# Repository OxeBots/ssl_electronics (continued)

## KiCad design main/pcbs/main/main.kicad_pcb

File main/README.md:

# SSL Electronics - Oxebots

Electronics design for the RoboCup Soccer Small-Size League (SSL).

## System Architecture

*   **Main Board:** ESP32-based controller board.
*   **Power Board:** Power distribution and battery protection.
*   **Kicker Board:** Board that drives the solenoid through a capacitor bank charged up to 200V.

## Repository Structure

*   `/pcbs`: KiCad boards project files.
*   `/Libraries`: Custom symbols, footprints, and 3D models.
*   `/exported`: STEP and 3D exports.
*   `/datasheets`: Component documentation.

## Core Components

*   **Toolchain:** KiCad 9.0+
*   **MCU:** ESP32 38-pin
*   **RF:** NRF24L01+
*   **Sensors:** GY-85 (IMU), AS5600 (motor encoder), VL53L5X (ToF sensor)
*   **Motors:** BL48250 motor with driver board (for 24V).
*   **Solenoid:** 25X50TL (for 24V)

## Configuration

To resolve library dependencies in KiCad, you must configure the `OXEBOTS_SSL_LIB_DIR` path variable:

1.  Open KiCad.
2.  Go to **Preferences** > **Configure Paths...**
3.  Add a new entry (+ symbol):
    *   **Name:** `OXEBOTS_SSL_LIB_DIR`
    *   **Path:** Path to the `Libraries` folder in your local machine.

This ensures all schematic symbols, footprints, and 3D models are correctly linked.

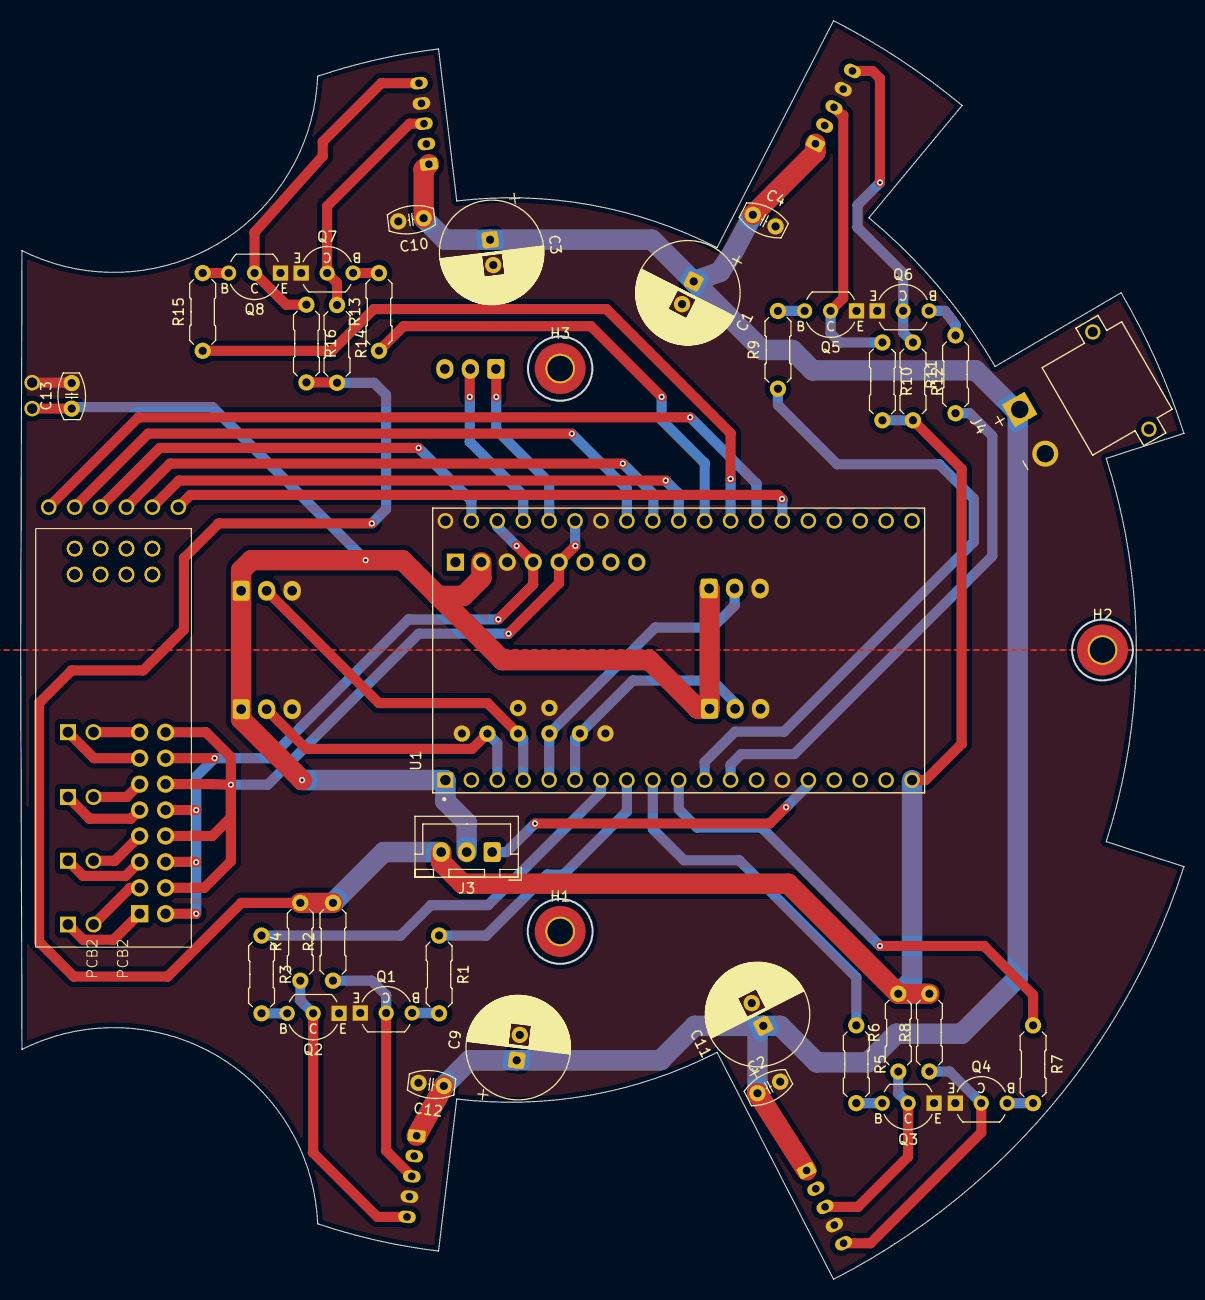
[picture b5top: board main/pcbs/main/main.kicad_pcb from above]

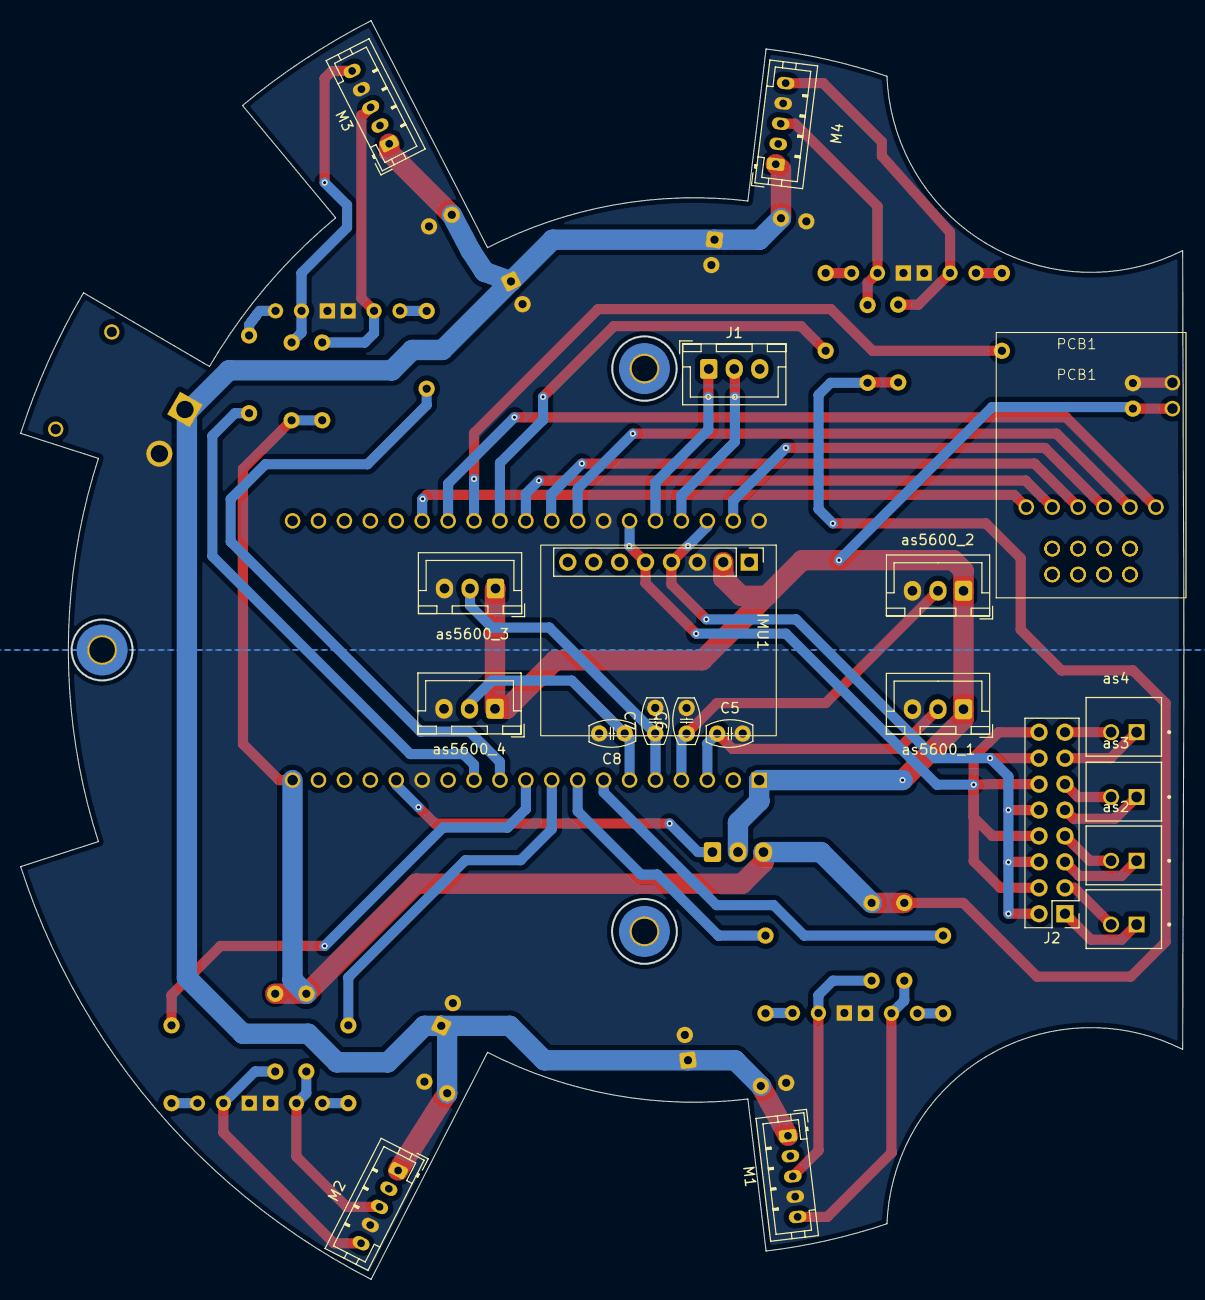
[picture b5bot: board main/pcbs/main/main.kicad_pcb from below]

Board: 2 copper layers, 114.0 x 123.3 mm, 60 parts (20 on the bottom side), 59 nets.

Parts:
C1, C3, C9, C11: 47uF; CP_Radial_D10.0mm_P2.50mm
C2, C4, C5, C6, C7, C8, C10, C12, C13: 100 nF; C_Disc_D5.0mm_W2.5mm_P2.50mm
H1, H2, H3: MountingHole; MountingHole_2.5mm_Pad_TopBottom
IMU1: GY 85; GY-085
J1, J3: JST_XH_B3B; JST_XH_B3B-XH-A_1x03_P2.50mm_Vertical
J2: Jumpers; PinHeader_2x08_P2.54mm_Vertical
J4: XT30PW-M; AMASS_XT30PW-M
M1, M2, M3, M4: HY-5_P2.00mm_Vertical
PCB1: NRF24L01_PWR_ADP
PCB2: NRF24L01
Q1, Q2, Q3, Q4, Q5, Q6, Q7, Q8: 2SC945; TO-92_Inline_Wide_ECB
R1, R2, R3, R4, R5, R6, R7, R8, R9, R10, R11, R12, R13, R14, R15, R16: 10k; R_Axial_DIN0207_L6.3mm_D2.5mm_P7.62mm_Horizontal
U1: ESP32-DEVKITC-32U; MODULE_ESP32-DEVKITC-32U
as1: M1_ENC_I2C; JST_B2B-XH-A
as2: M2_ENC_I2C; JST_B2B-XH-A
as3: M3_ENC_I2C; JST_B2B-XH-A
as4: M4_ENC_I2C; JST_B2B-XH-A
as5600_1: M1_ENC_AN; JST_XH_B3B-XH-A_1x03_P2.50mm_Vertical
as5600_2: M2_ENC_AN; JST_XH_B3B-XH-A_1x03_P2.50mm_Vertical
as5600_3: M3_ENC_AN; JST_XH_B3B-XH-A_1x03_P2.50mm_Vertical
as5600_4: M4_ENC_AN; JST_XH_B3B-XH-A_1x03_P2.50mm_Vertical

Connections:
+3.3V: C13.1, IMU1.2, J3.2, PCB1.15 (VCC), U1.1 (3V3), as5600_1.1, as5600_2.1, as5600_3.1, as5600_4.1
+5V: J3.3, R2.2, R4.2, R6.2, R8.2, R10.2, R12.2, R14.2, R16.2, U1.19 (EXT_5V)
+24V: C1.1, C2.1, C3.1, C4.1, C9.1, C10.1, C11.1, C12.1, J4.P, M1.1 (VCC), M2.1 (VCC), M3.1 (VCC), M4.1 (VCC)
/esp32/I2C.SCL: IMU1.4, J2.2, J2.6, J2.10, J2.14, U1.36 (IO22)
/esp32/I2C.SDA: IMU1.5, J2.4, J2.8, J2.12, J2.16, U1.33 (IO21)
/esp32/KICKER_EN: J1.1, U1.34 (RXD0)
/esp32/KICKER_PWM: J1.2, U1.35 (TXD0)
/esp32/M1_DIR: R1.1, U1.8 (IO33)
/esp32/M1_ENC: C5.1, U1.3 (SENSOR_VP), as5600_1.2
/esp32/M1_PWM: R3.1, U1.7 (IO32)
/esp32/M2_DIR: R5.1, U1.9 (IO25)
/esp32/M2_ENC: C6.1, U1.4 (SENSOR_VN), as5600_2.2
/esp32/M2_PWM: R7.1, U1.10 (IO26)
/esp32/M3_DIR: R9.1, U1.11 (IO27)
/esp32/M3_ENC: C7.1, U1.5 (IO34), as5600_3.2
/esp32/M3_PWM: R11.1, U1.12 (IO14)
/esp32/M4_DIR: R13.1, U1.28 (IO17)
/esp32/M4_ENC: C8.1, U1.6 (IO35), as5600_4.2
/esp32/M4_PWM: R15.1, U1.27 (IO16)
/esp32/RADIO.CE: PCB1.9 (CE_{mcu}), U1.25 (IO0)
/esp32/RADIO.CLK: PCB1.11 (SCK_{mcu}), U1.30 (IO18)
/esp32/RADIO.CS: PCB1.10 (CSN_{mcu}), U1.29 (IO5)
/esp32/RADIO.IRQ: PCB1.14 (IRQ_{mcu}), U1.26 (IO4)
/esp32/RADIO.MISO: PCB1.13 (MISO_{mcu}), U1.31 (IO19)
/esp32/RADIO.MOSI: PCB1.12 (MOSI_{mcu}), U1.37 (IO23)
/esp32/V_{MON}: J3.1, U1.15 (IO13)
GND: C1.2, C2.2, C3.2, C4.2, C5.2, C6.2, C7.2, C8.2, C9.2, C10.2, C11.2, C12.2, C13.2, IMU1.3, J4.N, M1.4 (GND), M2.4 (GND), M3.4 (GND), M4.4 (GND), PCB1.16 (GND), Q1.1 (E), Q2.1 (E), Q3.1 (E), Q4.1 (E), Q5.1 (E), Q6.1 (E), Q7.1 (E), Q8.1 (E), U1.14 (GND1), U1.32 (GND2), U1.38 (GND3), as5600_1.3, as5600_2.3, as5600_3.3, as5600_4.3
unnamed: J2.1, as1.1
unnamed: J2.3, as1.2
unnamed: J2.5, as2.1
unnamed: J2.7, as2.2
unnamed: J2.9, as3.1
unnamed: J2.11, as3.2
unnamed: J2.13, as4.1
unnamed: J2.15, as4.2
unnamed: M1.3 (DIR), Q1.2 (C), R2.1
unnamed: M1.5 (PWM), Q2.2 (C), R4.1
unnamed: M2.3 (DIR), Q3.2 (C), R6.1
unnamed: M2.5 (PWM), Q4.2 (C), R8.1
unnamed: M3.3 (DIR), Q5.2 (C), R10.1
unnamed: M3.5 (PWM), Q6.2 (C), R12.1
unnamed: M4.3 (DIR), Q7.2 (C), R14.1
unnamed: M4.5 (PWM), Q8.2 (C), R16.1
unnamed: PCB1.2 (CE), PCB2.2 (CE)
unnamed: PCB1.6 (CSN), PCB2.6 (CSN)
unnamed: PCB1.1 (GND_{out}), PCB2.1 (GND_{out})
unnamed: PCB1.8 (IRQ), PCB2.8 (IRQ)
unnamed: PCB1.4 (MISO), PCB2.4 (MISO)
unnamed: PCB1.7 (MOSI), PCB2.7 (MOSI)
unnamed: PCB1.3 (SCK), PCB2.3 (SCK)
unnamed: PCB1.5 (VCC_{out}), PCB2.5 (VCC_{out})
unnamed: Q1.3 (B), R1.2
unnamed: Q2.3 (B), R3.2
unnamed: Q3.3 (B), R5.2
unnamed: Q4.3 (B), R7.2
unnamed: Q5.3 (B), R9.2
unnamed: Q6.3 (B), R11.2
unnamed: Q7.3 (B), R13.2
unnamed: Q8.3 (B), R15.2

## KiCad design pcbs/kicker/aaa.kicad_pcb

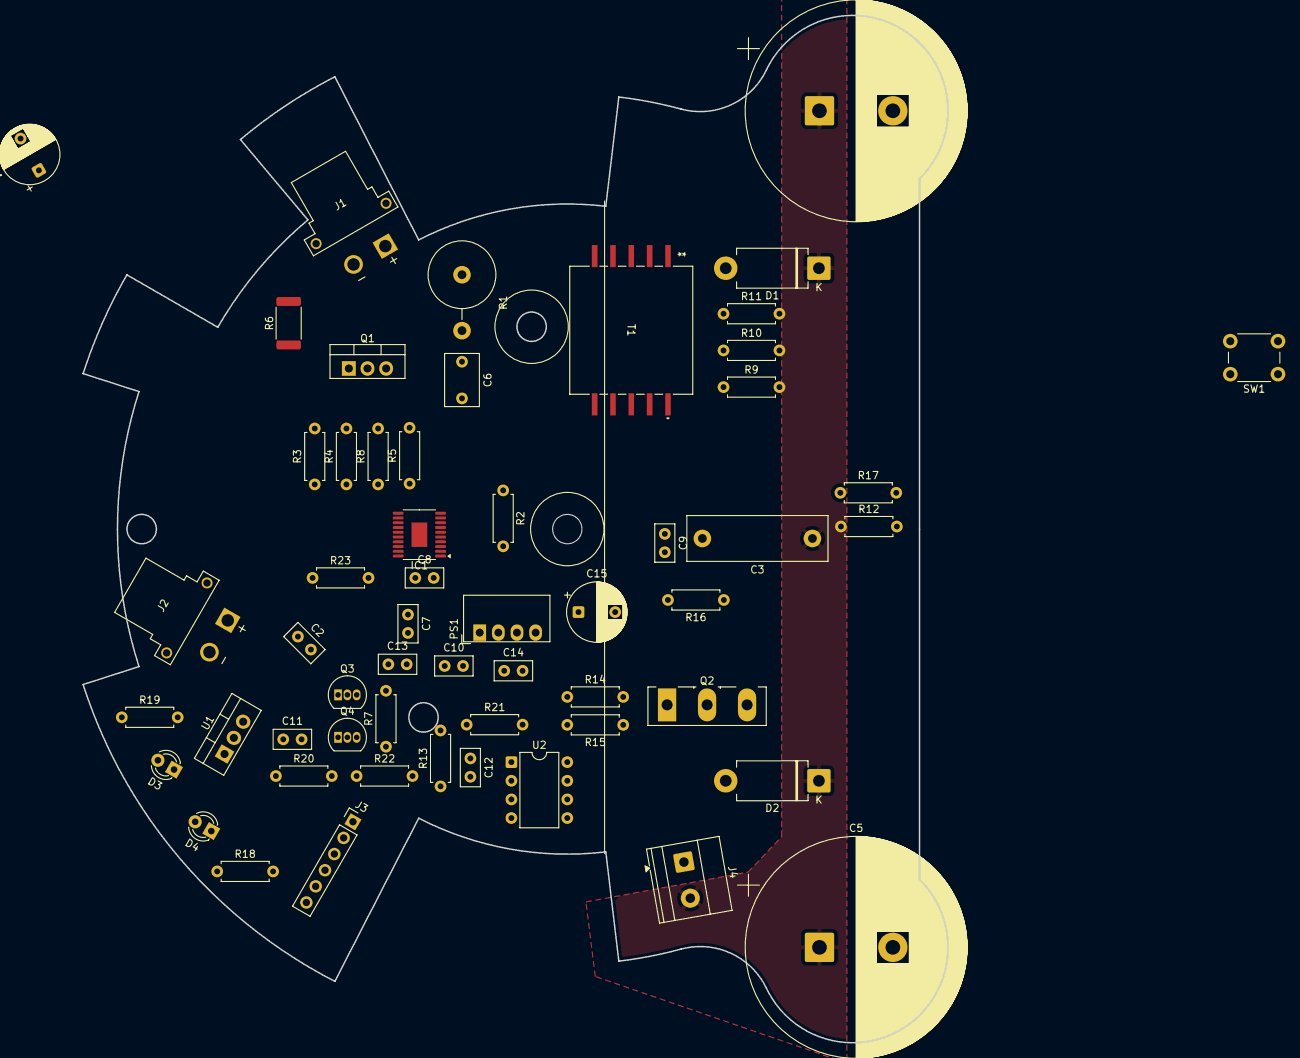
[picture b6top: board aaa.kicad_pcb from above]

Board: 2 copper layers, 117.9 x 140.0 mm, 56 parts (0 on the bottom side), 33 nets, no tracks yet.

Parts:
C1: 1000uF; CP_Radial_D8.0mm_P5.00mm
C2, C7, C8, C10, C11, C12, C13, C14: 100nF; C_Disc_D5.0mm_W2.5mm_P2.50mm
C3: 10nF; C_Rect_L19.0mm_W6.0mm_P15.00mm_MKS4
C4, C5: 100uF; CP_Radial_D30.0mm_P10.00mm_SnapIn
C6: 22nF; C_Rect_L7.0mm_W4.5mm_P5.00mm
C9: 10nF; C_Disc_D5.0mm_W2.5mm_P2.50mm
C15: 220uF; CP_Radial_D8.0mm_P5.00mm
D1, D2: MUR460; D_DO-201AD_P12.70mm_Horizontal
D3, D4: LED; LED_D3.0mm_Clear
IC1: LT3751; TSSOP-20-1EP_4.4x6.5mm_P0.65mm_EP2.15x3.35mm
J1, J2: XT30PW-F; AMASS_XT30PW-F
J3: PinHeader_1x06_P2.54mm_Vertical
J4: SOL; TerminalBlock_Phoenix_MKDS-1,5-2_1x02_P5.00mm_Horizontal
PS1: B1215S; Converter_DCDC_Murata_MEE1SxxxxSC_THT
Q1: IRFB4227; TO-220-3_Vertical
Q2: FGH60N60SMD; TO-247-3_Vertical
Q3, Q4: BC547; TO-92_Inline
R1: 4,7K; R_Axial_DIN0922_L20.0mm_D9.0mm_P7.62mm_Vertical
R2, R4: 39K; R_Axial_DIN0207_L6.3mm_D2.5mm_P7.62mm_Horizontal
R3: 18K; R_Axial_DIN0207_L6.3mm_D2.5mm_P7.62mm_Horizontal
R5: 10R; R_Axial_DIN0207_L6.3mm_D2.5mm_P7.62mm_Horizontal
R6: 25m (NOTA 1); R_2512_6332Metric
R7, R13: 220R; R_Axial_DIN0207_L6.3mm_D2.5mm_P7.62mm_Horizontal
R8: 1,5K; R_Axial_DIN0207_L6.3mm_D2.5mm_P7.62mm_Horizontal
R9, R10, R11: ?; R_Axial_DIN0207_L6.3mm_D2.5mm_P7.62mm_Horizontal
R12: 1M; R_Axial_DIN0207_L6.3mm_D2.5mm_P7.62mm_Horizontal
R14, R15, R16, R17: R; R_Axial_DIN0207_L6.3mm_D2.5mm_P7.62mm_Horizontal
R18, R19: 1K; R_Axial_DIN0207_L6.3mm_D2.5mm_P7.62mm_Horizontal
R20, R21, R22, R23: 10K; R_Axial_DIN0207_L6.3mm_D2.5mm_P7.62mm_Horizontal
SW1: SW_Push; SW_PUSH_6mm_H7.3mm
T1: DCT15EFD-U44S003; TRANS_U44S003_TDK
U1: LM7805_TO220; TO-220-3_Vertical
U2: HCPL-3120; DIP-8_W7.62mm

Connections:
+5V: C11.1, R18.1, R19.1, R20.1, R22.1, U1.3 (VO)
+15V_SEC: C14.1, C15.1, PS1.4 (+Vout), U2.8 (VCC)
DONE: IC1.7 (~DONE), Q3.2 (B), R20.2
FAULT: IC1.6 (~FAULT), Q4.2 (B), R22.2
FB: C9.1, IC1.10 (FB), R16.2, R17.1
MCU_IN_ENABLE: J3.1, R7.1
MCU_IN_KICK: J3.2, R13.1
MCU_OUT_DONE: J3.5, R21.2
MCU_OUT_FAULT: J3.4, R23.2
unnamed: C6.1, R1.2
unnamed: D1.2 (A), T1.1
unnamed: D2.2 (A), J4.1, Q2.2 (C)
unnamed: D3.2 (A), R18.2
unnamed: D3.1 (K), Q3.1 (C), R21.1
unnamed: D4.2 (A), R19.2
unnamed: D4.1 (K), Q4.1 (C), R23.1
unnamed: IC1.8 (CHARGE), R7.2
unnamed: IC1.12 (CSP), Q1.3 (S), R6.1
unnamed: IC1.15 (HVGATE), R5.1
unnamed: IC1.16 (RBG), R8.1
unnamed: IC1.20 (RDCM), R3.1
unnamed: IC1.18 (RVOUT), R4.1
unnamed: IC1.1 (RVTRANS), R2.2
unnamed: C6.2, Q1.2 (D), R3.2, R4.2, T1.6, T1.7
unnamed: Q1.1 (G), R5.2
unnamed: Q2.1 (G), R14.2, R15.1
unnamed: R9.2, R10.2, R11.2, SW1.2
unnamed: R14.1, U2.6 (VO), U2.7 (VO)
unnamed: C12.1, R13.2, U2.2 (A)
OVLO_1: C1.2, C2.2, C3.2, C4.2, C5.2, C7.2, C8.2, C9.2, C10.2, C11.2, C12.2, C13.2, C14.2, C15.2, IC1.3 (OVLO1), IC1.5 (OVLO2), IC1.9 (CLAMP), IC1.11 (CSN), IC1.21 (GND), J1.N, J2.N, J3.6, PS1.1 (-Vin), PS1.3 (-Vout), Q2.3 (E), Q3.3 (E), Q4.3 (E), R6.2, R8.2, R12.2, R15.2, R17.2, SW1.1, T1.10, U1.2 (GND), U2.3 (C), U2.5 (VEE)
UVLO_1: C1.1, C2.1, IC1.2 (UVLO1), J1.P, R1.1, R2.1, T1.4, T1.5
UVLO_2: C7.1, C8.1, C10.1, C13.1, IC1.4 (UVLO2), IC1.13 (VCC), IC1.14 (LVGATE), J2.P, PS1.2 (+Vin), U1.1 (VI)
VCAP: C3.1, C4.1, C5.1, D1.1 (K), D2.1 (K), J4.2, R9.1, R10.1, R11.1, R12.1, R16.1

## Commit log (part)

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2025-05-05 Add structure and files for the prototypes
2025-05-24 First version with 12x8 cm proofboard.
2025-10-03 Add power board
2025-10-03 Edits for custom board
2025-10-05 Added Kicker PCB
2025-10-05 feat: radio and motor encoders
2025-10-05 feat: imu
2025-10-06 Update for CNC
2025-10-06 fea: add jumpers to I2C encoders config
2025-10-06 Add NRF24L01 footprints & symbols
2025-10-06 wip: change radio footprint
2025-10-07 Created PCB for footprint tests
2025-10-07 feat: association of footprints
2025-10-07 Add BOM & gcode for manufacturing
2025-10-08 Start layout
2025-10-08 Fix jumpers
2025-10-08 Preliminary placing components
2025-10-08 Add step file
2025-10-09 feat: roteamento do main PCB
2025-10-09 Add manufacturing files for tester board
2025-10-09 Re-routing
2026-01-30 First commit of Kicker Board
2026-01-30 Updated Solenoid Circuit
2026-01-30 Included datasheets
    Included datasheets of AQV454 and LT3751
2026-02-06 Alteração GY-85
2026-02-06 arquivo base para placa
2026-02-08 Conserto do nome
2026-02-08 Mensagem de teste
2026-02-08 Update repo README and main PCB title header
2026-02-11 alteração antena
2026-03-03 correção nrf24lo1
2026-03-18 Updated feedback circuit
2026-04-04 main
2026-04-04 feat: implementa lógica do shift register para encoders e chute
2026-04-04 ref: vincula subpasta main ao projeto principal
2026-04-05 ref: ajustes finos no esquemático e firmware de calibração
2026-04-05 feat: esquemático
2026-04-13 Refactor power distribution board with TPS5430 integrated design
2026-04-24 Fix pcb
2026-05-25 adding ldo regulador to radio
2026-05-25 Add TOF symbol and refactor the schematic to be cleaner
2026-05-25 Update footprint for TOF and encoders
2026-06-09 Add 74HC595 shift register into the schematic
2026-06-27 update
    Placa parcialmente desenhada, componentes posicionados
